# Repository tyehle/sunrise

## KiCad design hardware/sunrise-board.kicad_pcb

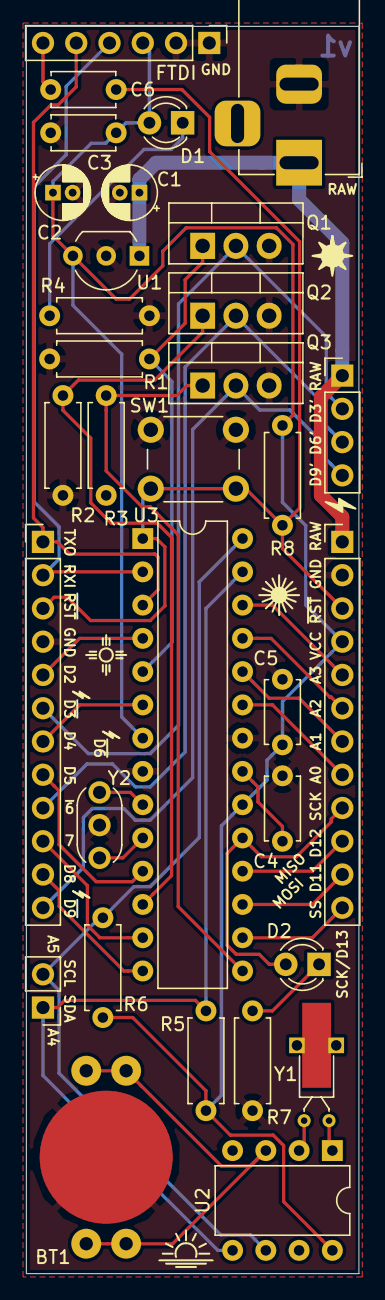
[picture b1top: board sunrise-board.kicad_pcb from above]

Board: 2 copper layers, 25.4 x 95.2 mm, 32 parts (0 on the bottom side), 36 nets.

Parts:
BT1: CR1220 3.3V; BatteryHolder_CR1220_THT
C1, C2: 10uF; CP_Radial_D4.0mm_P1.50mm
C3, C4, C5, C6: 0.1uF; C_Disc_D4.7mm_W2.5mm_P5.00mm
D1, D2: LED; LED_D3.0mm
J1: Barrel Jack 12V; BarrelJack_Horizontal
J2, J4: Header; PinHeader_1x12_P2.54mm_Vertical
J3: FTDI Basic; PinHeader_1x06_P2.54mm_Vertical
J5: LED_STRIP_VGRB; PinHeader_1x04_P2.54mm_Vertical
J6: I2C; PinHeader_1x02_P2.54mm_Vertical
Q1, Q2, Q3: IRLZ34N; TO-220-3_Vertical
R1, R2, R3: 10k; R_Axial_DIN0207_L6.3mm_D2.5mm_P7.62mm_Horizontal
R4, R5, R6, R8: 10K; R_Axial_DIN0207_L6.3mm_D2.5mm_P7.62mm_Horizontal
R7: 330; R_Axial_DIN0207_L6.3mm_D2.5mm_P7.62mm_Horizontal
SW1: Reset; SW_PUSH_6mm
U1: L4931CZ50-AP; TO-92_Inline_Wide
U2: DS1307+; DIP-8_W7.62mm
U3: ATmega328P-PU; DIP-28_W7.62mm
Y1: 32.768kHz; Crystal_C26-LF_D2.1mm_L6.5mm_Horizontal_1EP_style2
Y2: 16MHz; Resonator-3Pin_W6.0mm_H3.0mm

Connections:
A0: J4.8, U3.23
A1: J4.7, U3.24
A2: J4.6, U3.25
A3: J4.5, U3.26
D2: J2.5, U3.4
D4: J2.7, U3.6
D5: J2.8, U3.11
D7: J2.10, U3.13
D8: J2.11, U3.14
D10: J4.12, U3.16
DTR: C6.2, J3.6
GND: BT1.2, C1.2, C2.2, C3.2, C4.2, C5.2, J1.2, J2.4, J3.1, J3.2, J4.2, Q1.3, Q2.3, Q3.3, R1.2, R2.2, R3.2, R4.2, R7.1, SW1.1, U1.2, U2.4, U3.8, U3.22, Y2.2
LED_B: J2.12, J5.4, Q3.2
LED_CTL_B: Q3.1, R3.1, U3.15
LED_CTL_G: Q2.1, R2.1, U3.12
LED_CTL_R: Q1.1, R1.1, U3.5
LED_G: J2.9, J5.3, Q2.2
LED_R: J2.6, J5.2, Q1.2
MISO: J4.10, U3.18
MOSI: J4.11, U3.17
unnamed: BT1.1, U2.3
unnamed: C4.1, U3.21
unnamed: D1.1, R4.1
unnamed: D2.1, R7.2
unnamed: U2.1, Y1.1
unnamed: U2.2, Y1.2
unnamed: U3.9, Y2.3
unnamed: U3.10, Y2.1
RAW: C1.1, J1.1, J4.1, J5.1, U1.1
RESET: C6.1, J2.3, J4.3, R8.2, SW1.2, U3.1
RXI: J2.2, J3.4, U3.2
SCK: D2.2, J4.9, U3.19
SCL: J6.2, R6.2, U2.6, U3.28
SDA: J6.1, R5.2, U2.5, U3.27
TXO: J2.1, J3.5, U3.3
VCC: C2.1, C3.1, C5.1, D1.2, J3.3, J4.4, R5.1, R6.1, R8.1, U1.3, U2.8, U3.7, U3.20

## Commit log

2018-11-22 add color python test bed
2018-11-22 add the data file needed for the colors
2018-11-22 add the whole data set
2018-11-22 plot rgb curves of the data
2018-11-23 write colors to a data file
2018-11-23 arduino project
2019-01-31 add rtc code
2019-02-14 all modes working
2019-06-01 small fixes to firmware
2019-06-01 add whitebalance photos
2019-06-01 Create LICENSE
2019-06-01 schematic done
2019-06-01 print the schematic
2019-06-02 update schematic and assign some footprints
2019-06-03 finish assigning footprints
2019-06-03 netlist and licences info
2019-06-03 update schematic pdf
2019-06-03 all nets and board outline done
2019-06-04 fill and silk screen done
2019-06-05 updates to silk screen
2019-06-14 update gerbers to include fab layer
2019-06-14 change schematic to svg
2019-06-14 add component placement images
2019-06-14 add board renders
2019-06-14 add a readme for the hardware
2019-06-14 fix typo
2019-06-25 finish bom and docs
2019-06-25 update schematic
2019-06-25 fix voltage regulator pins
2019-06-25 fix board layout
2019-06-26 regen gerbers
2019-06-26 regen schematic svg
2019-06-26 regen renders
2019-06-26 regen doc images
2019-06-26 regen assembly doc
2019-06-26 update assembly doc
2019-06-26 fix spelling errors
2019-06-27 update code for board
2020-05-08 make it easier to flash the clock time
2020-05-08 rename and clean up the hardware project
2020-05-08 move the firmware to its own folder
2020-05-10 fix crystal value
2020-05-14 smooth out the startup using the 16 bit pwm
2020-05-15 move the color viewing script back to this folder
2020-05-15 make just recipes for build and upload using the arduino-cli
2020-05-15 add a green flash and fix the 16 bit PWM writing
2020-05-15 move the pwm logic to its own file
2020-05-15 remove old mode code
2020-05-17 fix bugs with pwm file
2020-05-17 fix issues with the new way of triggering the lights
2020-05-19 use the exponential brightness map and make the updates chatty again
2020-05-19 produce better plots
2020-05-19 ignore vscode files
2020-05-21 fix an overflow bug
2020-06-07 plot a histogram of raw colors
2020-06-07 fix the fonts on the hist plot
2020-06-07 fix the fonts on the color plots
2020-06-07 remove old font code
2020-06-08 change normalization plot title
2020-10-15 add toolchain install to justfile

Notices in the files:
hardware/sunrise-board.kicad_pcb:
License: CC BY-NC-SA
